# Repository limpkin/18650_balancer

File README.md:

# 18650_balancer
18650 cells balancer

From https://www.limpkin.fr/index.php?post/2023/04/29/Assembling-a-Custom-48V-18650-Battery
If you're planning to make one of these, make sure to get the right 18650 cell holder, as the new ones are wider than the one used in this project.

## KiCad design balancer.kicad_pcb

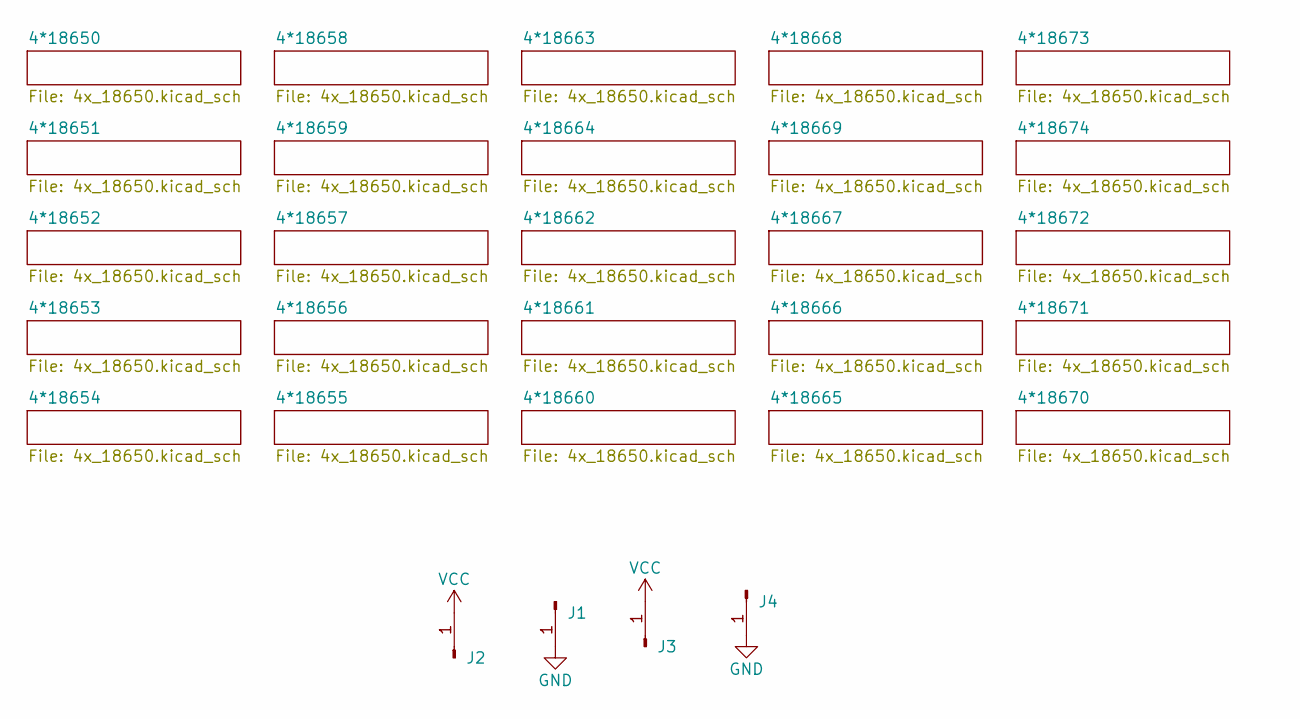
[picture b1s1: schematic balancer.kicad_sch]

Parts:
J1, J2, J3, J4: Conn_01x01_Pin; Wuerth_REDCUBE-THR_WP-THRBU_74655095_THR

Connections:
GND: J1.1, J4.1; also elsewhere on the board
VCC: J2.1, J3.1; also elsewhere on the board

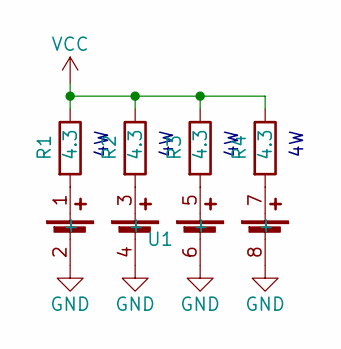
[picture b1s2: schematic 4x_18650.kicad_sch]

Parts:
R1, R2, R3, R4: 4.3; R_2816_7142Metric
U1: 4x_18650_smd

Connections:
GND: U1.2 (-), U1.4 (-), U1.6 (-), U1.8 (-); also elsewhere on the board
unnamed: R1.2, U1.1 (+)
unnamed: R2.2, U1.3 (+)
unnamed: R3.2, U1.5 (+)
unnamed: R4.2, U1.7 (+)
VCC: R1.1, R2.1, R3.1, R4.1; also elsewhere on the board

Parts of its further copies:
R5, R6, R7, R8, R9, R10, R11, R12, R13, R14, R15, R16, R17, R18, R19, R20, R21, R22, R23, R24, R25, R26, R27, R28, R29, R30, R31, R32, R33, R34, R35, R36, R37, R38, R39, R40, R41, R42, R43, R44, R45, R46, R47, R48, R49, R50, R51, R52, R53, R54, R55, R56, R57, R58, R59, R60, R61, R62, R63, R64, R65, R66, R67, R68, R69, R70, R71, R72, R73, R74, R75, R76, R77, R78, R79, R80, R81, R82, R83, R84, R85, R86, R87, R88, R89, R90, R91, R92, R93, R94, R95, R96, R97, R98, R99, R100: 4.3; R_2816_7142Metric
U2, U3, U4, U5, U6, U7, U8, U9, U10, U11, U12, U13, U14, U15, U16, U17, U18, U19, U20, U21, U22, U23, U24, U25: 4x_18650_smd

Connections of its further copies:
GND: U2.2 (-), U2.4 (-), U2.6 (-), U2.8 (-), U3.2 (-), U3.4 (-), U3.6 (-), U3.8 (-), U4.2 (-), U4.4 (-), U4.6 (-), U4.8 (-), U5.2 (-), U5.4 (-), U5.6 (-), U5.8 (-), U6.2 (-), U6.4 (-), U6.6 (-), U6.8 (-), U7.2 (-), U7.4 (-), U7.6 (-), U7.8 (-), U8.2 (-), U8.4 (-), U8.6 (-), U8.8 (-), U9.2 (-), U9.4 (-), U9.6 (-), U9.8 (-), U10.2 (-), U10.4 (-), U10.6 (-), U10.8 (-), U11.2 (-), U11.4 (-), U11.6 (-), U11.8 (-), U12.2 (-), U12.4 (-), U12.6 (-), U12.8 (-), U13.2 (-), U13.4 (-), U13.6 (-), U13.8 (-), U14.2 (-), U14.4 (-), U14.6 (-), U14.8 (-), U15.2 (-), U15.4 (-), U15.6 (-), U15.8 (-), U16.2 (-), U16.4 (-), U16.6 (-), U16.8 (-), U17.2 (-), U17.4 (-), U17.6 (-), U17.8 (-), U18.2 (-), U18.4 (-), U18.6 (-), U18.8 (-), U19.2 (-), U19.4 (-), U19.6 (-), U19.8 (-), U20.2 (-), U20.4 (-), U20.6 (-), U20.8 (-), U21.2 (-), U21.4 (-), U21.6 (-), U21.8 (-), U22.2 (-), U22.4 (-), U22.6 (-), U22.8 (-), U23.2 (-), U23.4 (-), U23.6 (-), U23.8 (-), U24.2 (-), U24.4 (-), U24.6 (-), U24.8 (-), U25.2 (-), U25.4 (-), U25.6 (-), U25.8 (-); also elsewhere on the board
unnamed: R5.2, U2.1 (+)
unnamed: R6.2, U2.3 (+)
unnamed: R7.2, U2.5 (+)
unnamed: R8.2, U2.7 (+)
unnamed: R9.2, U3.1 (+)
unnamed: R10.2, U3.3 (+)
unnamed: R11.2, U3.5 (+)
unnamed: R12.2, U3.7 (+)
unnamed: R13.2, U4.1 (+)
unnamed: R14.2, U4.3 (+)
unnamed: R15.2, U4.5 (+)
unnamed: R16.2, U4.7 (+)
unnamed: R17.2, U5.1 (+)
unnamed: R18.2, U5.3 (+)
unnamed: R19.2, U5.5 (+)
unnamed: R20.2, U5.7 (+)
unnamed: R21.2, U6.1 (+)
unnamed: R22.2, U6.3 (+)
unnamed: R23.2, U6.5 (+)
unnamed: R24.2, U6.7 (+)
unnamed: R25.2, U7.1 (+)
unnamed: R26.2, U7.3 (+)
unnamed: R27.2, U7.5 (+)
unnamed: R28.2, U7.7 (+)
unnamed: R29.2, U8.1 (+)
unnamed: R30.2, U8.3 (+)
unnamed: R31.2, U8.5 (+)
unnamed: R32.2, U8.7 (+)
unnamed: R33.2, U9.1 (+)
unnamed: R34.2, U9.3 (+)
unnamed: R35.2, U9.5 (+)
unnamed: R36.2, U9.7 (+)
unnamed: R37.2, U10.1 (+)
unnamed: R38.2, U10.3 (+)
unnamed: R39.2, U10.5 (+)
unnamed: R40.2, U10.7 (+)
unnamed: R41.2, U11.1 (+)
unnamed: R42.2, U11.3 (+)
unnamed: R43.2, U11.5 (+)
unnamed: R44.2, U11.7 (+)
unnamed: R45.2, U12.1 (+)
unnamed: R46.2, U12.3 (+)
unnamed: R47.2, U12.5 (+)
unnamed: R48.2, U12.7 (+)
unnamed: R49.2, U13.1 (+)
unnamed: R50.2, U13.3 (+)
unnamed: R51.2, U13.5 (+)
unnamed: R52.2, U13.7 (+)
unnamed: R53.2, U14.1 (+)
unnamed: R54.2, U14.3 (+)
unnamed: R55.2, U14.5 (+)
unnamed: R56.2, U14.7 (+)
unnamed: R57.2, U15.1 (+)
unnamed: R58.2, U15.3 (+)
unnamed: R59.2, U15.5 (+)
unnamed: R60.2, U15.7 (+)
unnamed: R61.2, U16.1 (+)
unnamed: R62.2, U16.3 (+)
unnamed: R63.2, U16.5 (+)
unnamed: R64.2, U16.7 (+)
unnamed: R65.2, U17.1 (+)
unnamed: R66.2, U17.3 (+)
unnamed: R67.2, U17.5 (+)
unnamed: R68.2, U17.7 (+)
unnamed: R69.2, U18.1 (+)
unnamed: R70.2, U18.3 (+)
unnamed: R71.2, U18.5 (+)
unnamed: R72.2, U18.7 (+)
unnamed: R73.2, U19.1 (+)
unnamed: R74.2, U19.3 (+)
unnamed: R75.2, U19.5 (+)
unnamed: R76.2, U19.7 (+)
unnamed: R77.2, U20.1 (+)
unnamed: R78.2, U20.3 (+)
unnamed: R79.2, U20.5 (+)
unnamed: R80.2, U20.7 (+)
unnamed: R81.2, U21.1 (+)
unnamed: R82.2, U21.3 (+)
unnamed: R83.2, U21.5 (+)
unnamed: R84.2, U21.7 (+)
unnamed: R85.2, U22.1 (+)
unnamed: R86.2, U22.3 (+)
unnamed: R87.2, U22.5 (+)
unnamed: R88.2, U22.7 (+)
unnamed: R89.2, U23.1 (+)
unnamed: R90.2, U23.3 (+)
unnamed: R91.2, U23.5 (+)
unnamed: R92.2, U23.7 (+)
unnamed: R93.2, U24.1 (+)
unnamed: R94.2, U24.3 (+)
unnamed: R95.2, U24.5 (+)
unnamed: R96.2, U24.7 (+)
unnamed: R97.2, U25.1 (+)
unnamed: R98.2, U25.3 (+)
unnamed: R99.2, U25.5 (+)
unnamed: R100.2, U25.7 (+)
VCC: R5.1, R6.1, R7.1, R8.1, R9.1, R10.1, R11.1, R12.1, R13.1, R14.1, R15.1, R16.1, R17.1, R18.1, R19.1, R20.1, R21.1, R22.1, R23.1, R24.1, R25.1, R26.1, R27.1, R28.1, R29.1, R30.1, R31.1, R32.1, R33.1, R34.1, R35.1, R36.1, R37.1, R38.1, R39.1, R40.1, R41.1, R42.1, R43.1, R44.1, R45.1, R46.1, R47.1, R48.1, R49.1, R50.1, R51.1, R52.1, R53.1, R54.1, R55.1, R56.1, R57.1, R58.1, R59.1, R60.1, R61.1, R62.1, R63.1, R64.1, R65.1, R66.1, R67.1, R68.1, R69.1, R70.1, R71.1, R72.1, R73.1, R74.1, R75.1, R76.1, R77.1, R78.1, R79.1, R80.1, R81.1, R82.1, R83.1, R84.1, R85.1, R86.1, R87.1, R88.1, R89.1, R90.1, R91.1, R92.1, R93.1, R94.1, R95.1, R96.1, R97.1, R98.1, R99.1, R100.1; also elsewhere on the board

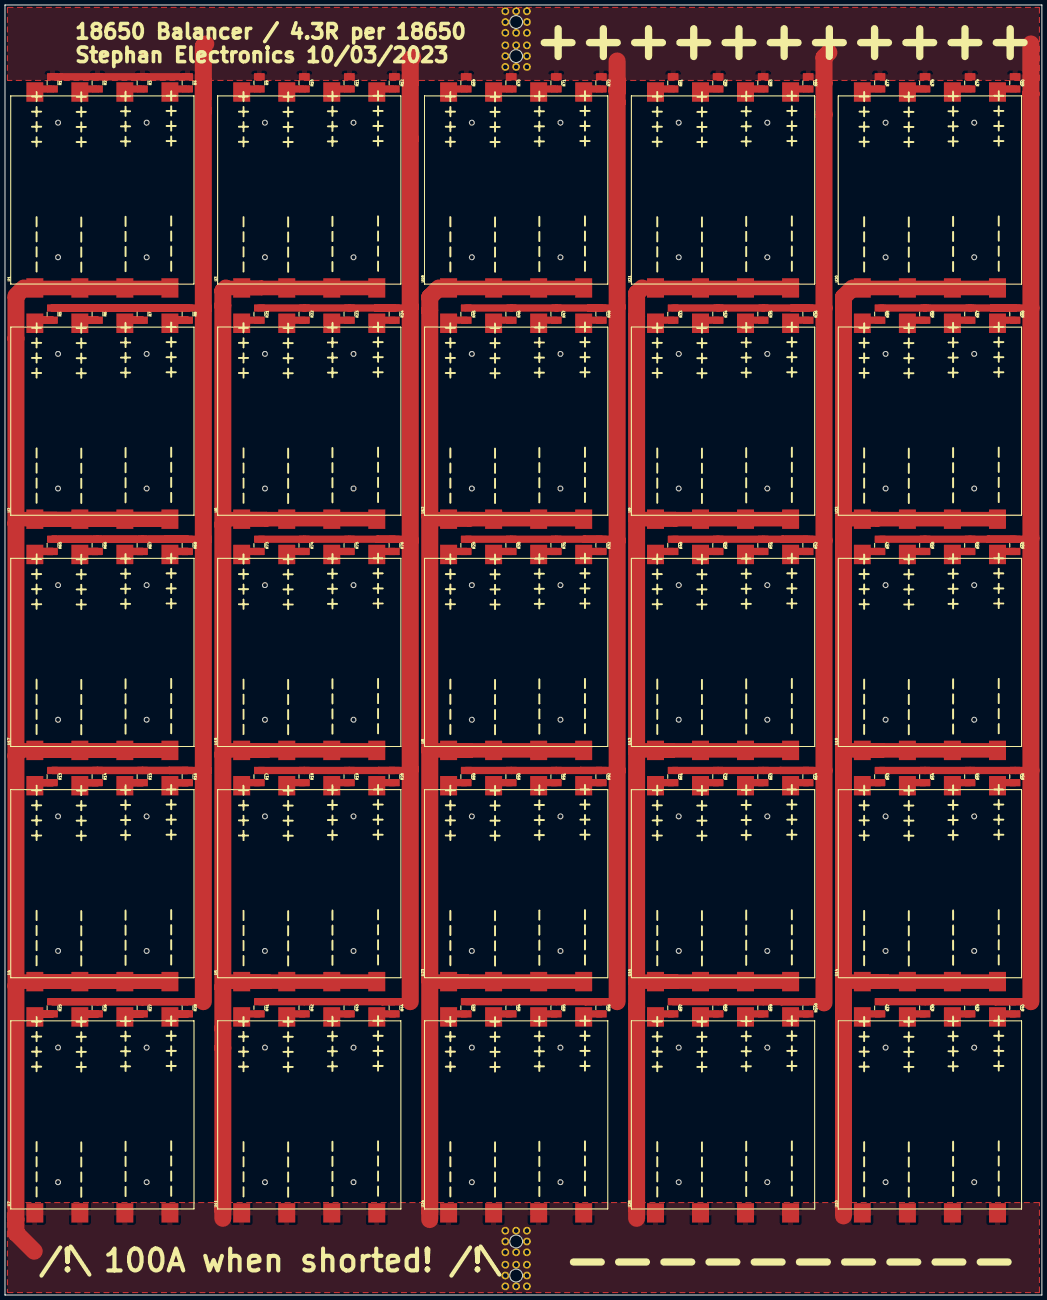
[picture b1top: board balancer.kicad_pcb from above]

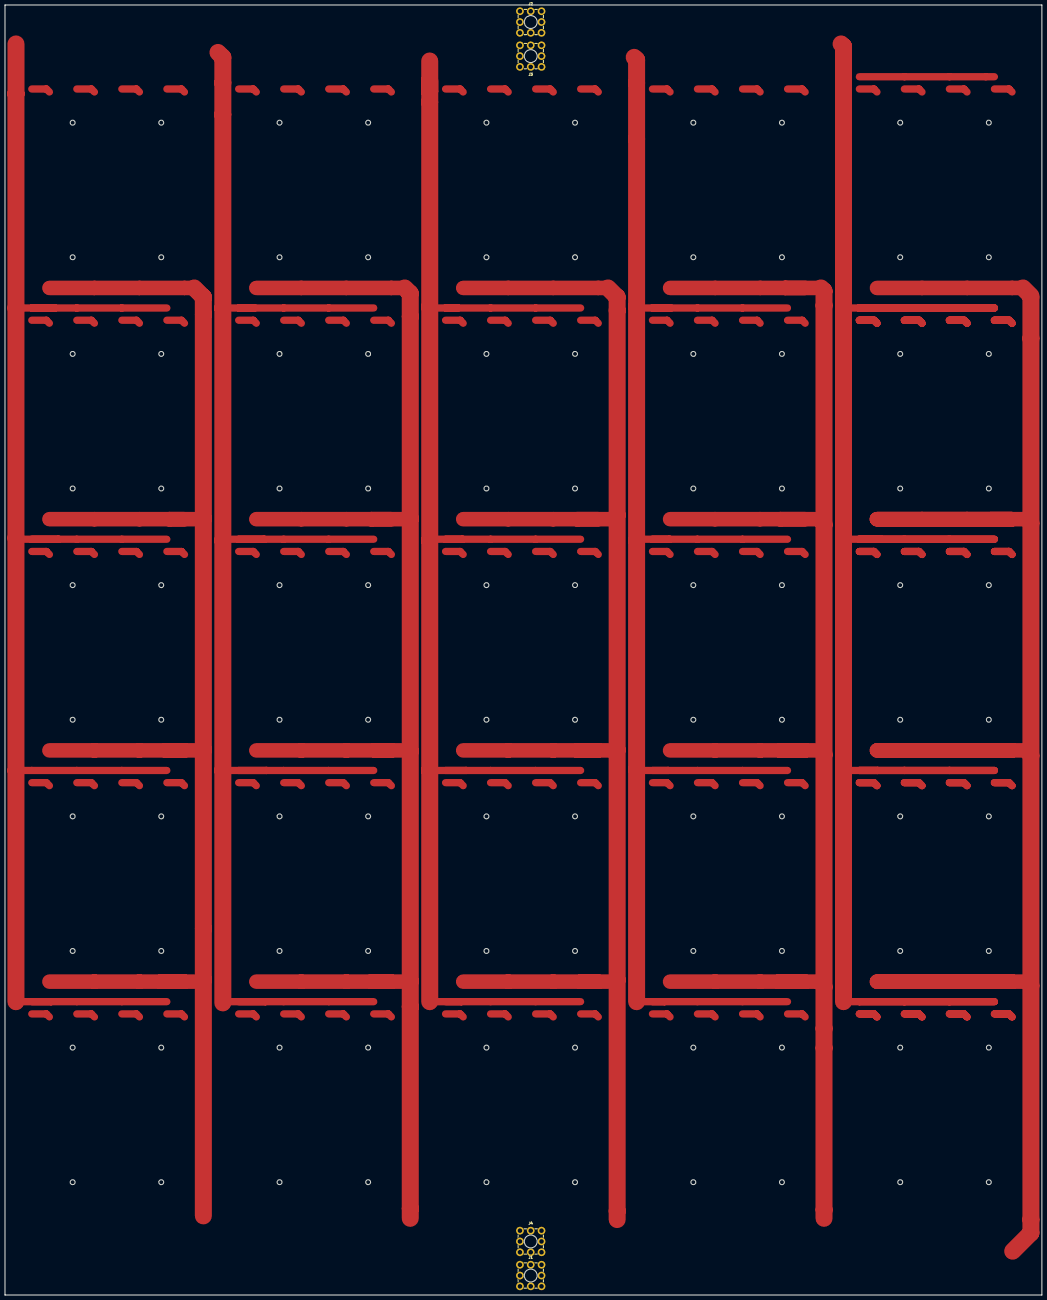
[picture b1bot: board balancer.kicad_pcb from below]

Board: 2 copper layers, 426.0 x 530.0 mm, 129 parts (4 on the bottom side), 102 nets.

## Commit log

2023-12-02 quick note
